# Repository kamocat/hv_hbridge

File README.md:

# hv_hbridge
High voltage hbridge for AC or DC control

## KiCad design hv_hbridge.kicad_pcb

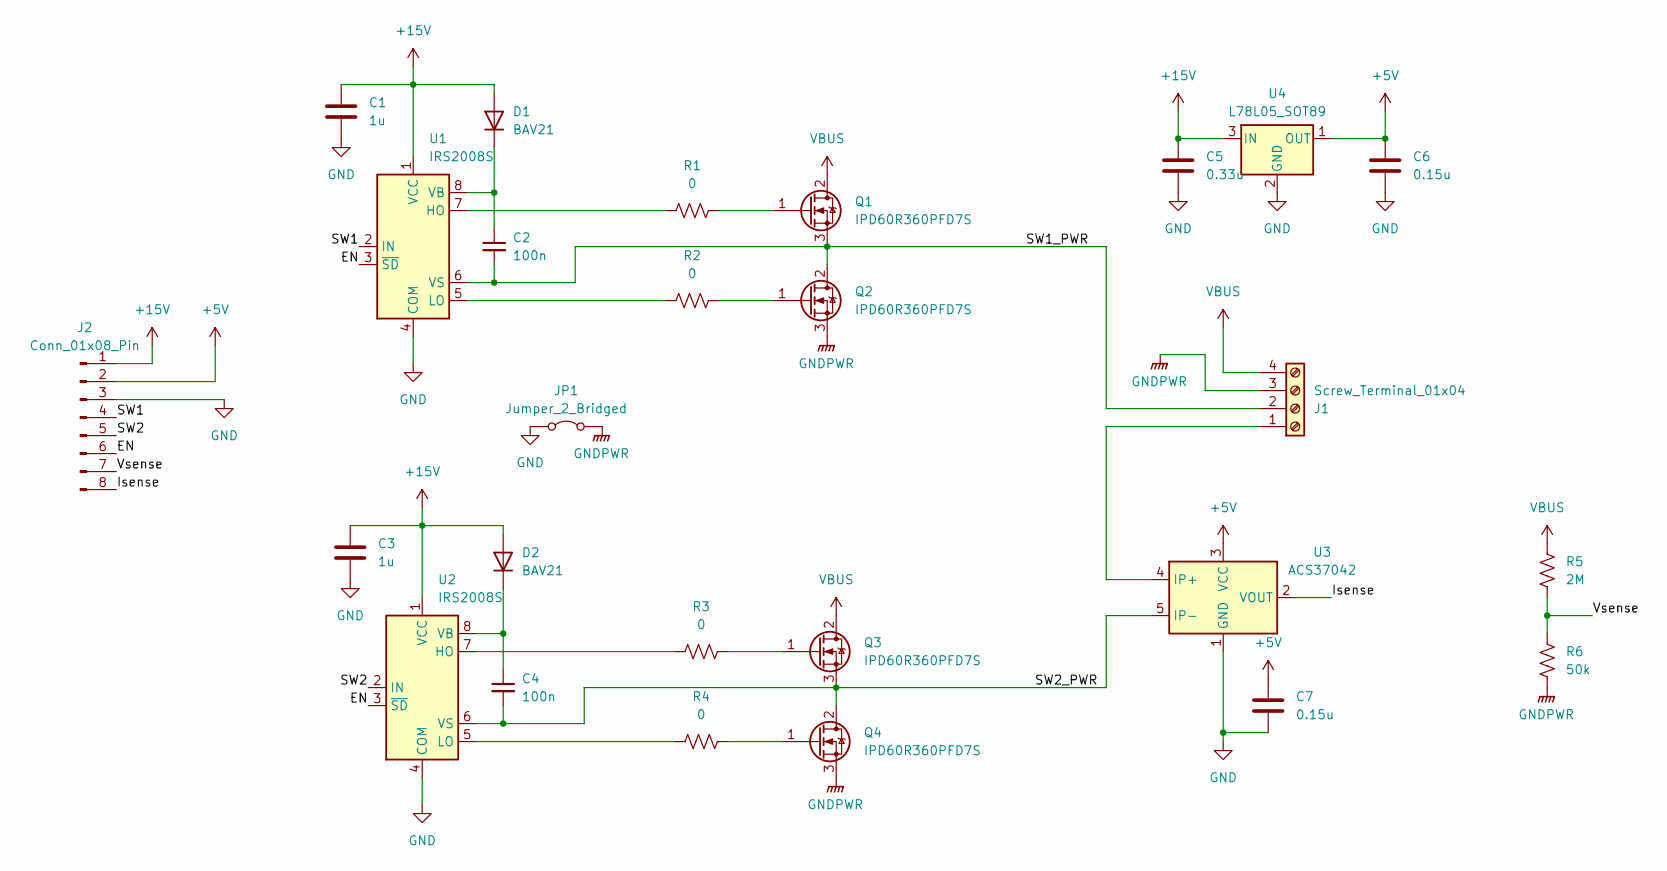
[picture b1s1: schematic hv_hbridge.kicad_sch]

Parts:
C1, C3: 1u; C_0805_2012Metric
C2, C4: 100n; C_1206_3216Metric
C5: 0.33u; C_0805_2012Metric
C6, C7: 0.15u; C_0805_2012Metric
D1, D2: BAV21; D_SOD-323
J1: Screw_Terminal_01x04; Altech_AK100_1x04_P5.00mm
J2: Conn_01x08_Pin; PinHeader_1x08_P2.54mm_Vertical
JP1: Jumper_2_Bridged; TestPoint_2Pads_Pitch2.54mm_Drill0.8mm
Q1, Q2, Q3, Q4: IPD60R360PFD7S; TO-252-2
R1, R2, R3, R4: 0; R_0805_2012Metric
R5: 2M; R_1206_3216Metric
R6: 50k; R_0805_2012Metric
U1, U2: IRS2008S; SOIC-8_3.9x4.9mm_P1.27mm
U3: ACS37042; SOT-23-5
U4: L78L05_SOT89; SOT-89-3

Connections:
+5V: C6.1, C7.1, J2.2, U3.3 (VCC), U4.1 (OUT)
+15V: C1.1, C3.1, C5.1, D1.2 (A), D2.2 (A), J2.1, U1.1 (VCC), U2.1 (VCC), U4.3 (IN)
/EN: J2.6, U1.3 (~SD), U2.3 (~SD)
/Isense: J2.8, U3.2 (VOUT)
/SW1: J2.4, U1.2 (IN)
/SW1_PWR: C2.2, J1.2, Q1.3 (S), Q2.2 (D), U1.6 (VS)
/SW2: J2.5, U2.2 (IN)
/SW2_PWR: C4.2, Q3.3 (S), Q4.2 (D), U2.6 (VS), U3.5 (IP-)
/Vsense: J2.7, R5.2, R6.1
GND: C1.2, C3.2, C5.2, C6.2, C7.2, J2.3, JP1.1 (A), U1.4 (COM), U2.4 (COM), U3.1 (GND), U4.2 (GND)
GNDPWR: J1.3, JP1.2 (B), Q2.3 (S), Q4.3 (S), R6.2
unnamed: C2.1, D1.1 (K), U1.8 (VB)
unnamed: C4.1, D2.1 (K), U2.8 (VB)
unnamed: J1.1, U3.4 (IP+)
unnamed: Q1.1 (G), R1.2
unnamed: Q2.1 (G), R2.2
unnamed: Q3.1 (G), R3.2
unnamed: Q4.1 (G), R4.2
unnamed: R1.1, U1.7 (HO)
unnamed: R2.1, U1.5 (LO)
unnamed: R3.1, U2.7 (HO)
unnamed: R4.1, U2.5 (LO)
VBUS: J1.4, Q1.2 (D), Q3.2 (D), R5.1

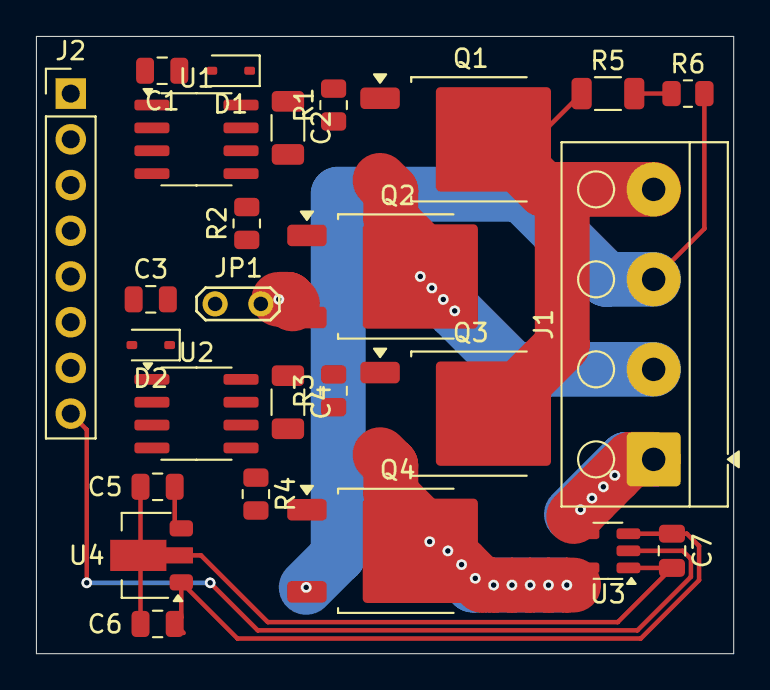
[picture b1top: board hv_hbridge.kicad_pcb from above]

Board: 2 copper layers, 38.7 x 34.3 mm, 26 parts (0 on the bottom side), 23 nets.

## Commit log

2025-08-09 Schematic complete, routing traces
